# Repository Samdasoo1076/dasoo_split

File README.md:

# choc-split-60 ⌨️

로우스태거(row‑staggered) 배열을 좌우로 나눈 **스플릿 키보드**입니다.
Kailh **Choc v2(CPG1353) 로우프로파일 핫스왑** 스위치 **71개 + 로터리 인코더 1개 = 72키 포지션**
(좌 34 / 우 38), 좌우 각각 **RP2040 Pro Micro**, 안쪽 상단의 **USB-C 링크 포트**로 좌우를 잇고,
`COL2ROW` 매트릭스를 씁니다.
모든 PCB 배선은 자동 라우터 없이 좌표를 계산해 직접 배선했고, `scripts/verify_pcb.py`로 전수 검증합니다.

*(실물 느낌 렌더 — 위 도면 그대로의 배열입니다)*

*(KLE 형식 도면 — 좌우 행 오프셋과 0.25u 매크로 열 간격이 그대로 보입니다)*

*(PCB 미리보기: 빨강 = F.Cu, 파랑 = B.Cu, 흰 점 = 비아, 회색 = F.Silkscreen)*

*(좌 하프 회로도 — 스위치 33 + 다이오드 33, 컨트롤러 U1, USB-C 링크 J1, 리셋, EC11 인코더 RE1과 그 다이오드.
각 칸이 매트릭스의 (행, 열) 자리이고, 넷 이름이 그대로 적혀 있습니다)*

*(우 하프 회로도 — 스위치 38 + 다이오드 38, 컨트롤러·USB-C 링크·리셋. 아래쪽 두 줄의 `← ↓ →` 가 매트릭스
COL6·7·8 에 그대로 놓입니다)*

---

## 1. 보드 사양

| 항목 | 값 |
|---|---|
| 배열 | 65% 로우스태거 + 좌측 매크로 열 + 우측 방향키·Del, 좌우 분리 |
| 키 수 | 좌 33 스위치 + 인코더 1 / 우 38 스위치 = **스위치 71 + 엔코더 1 (72 포지션)** |
| 키 피치 | 19.05 mm (MX 표준 피치, Choc v2 스위치 + MX 호환 키캡) |
| 행 스태거 | 좌 `0 / 0.5u / 0.75u / 1.25u` · 우 `-0.5 / 0 / 0.25 / -0.5u` (Tab 1.5u·Caps 1.75u·LShift 2.25u·`\` 1.5u·RShift **1u**) |
| 분할 위치 | 숫자열 `6`\|`7`, 알파열 `T`\|`Y`, `G`\|`H` — 하단 알파열은 `B` 가 **양쪽 하프에 하나씩** 있습니다(아래 설명) |
| 매크로 열 | 좌측 최외곽 열에서 **0.25u(4.7625 mm)** 띄워 배치, 위→아래 `노브 → Home → End → PgUp → PgDn` |
| 방향키 | `RShift`(1u) 바로 오른쪽 `↑`, 그 아래 `↓`, `↑` 오른쪽에 `Del`, `Del`/`↓` 아래에 `→`, 그 왼쪽 `←`. `RCtrl` 과 `←` 사이는 **0.5u 빈칸**(예전 `RFn` 자리) |
| 스태빌라이저 | **2u 이상 키 5개**에 **Choc v2 PCB 마운트 스태빌**(Salicylic‑acid3 / Keeb‑On! 스크류 타입) — 좌 `LShift`(2.25u)·`Space`(2u) / 우 `BSpc`(2u)·`Enter`(2.25u)·`Space`(2.25u). 키마다 타원 홀 4개(3.2×3.4 / 3.0×4.0 mm, 중심에서 좌우 ±11.9 mm) + 하우징이 지나가는 **Edge.Cuts 컷아웃 2개**(x 8.9~14.9, y ±3.75 mm) = 홀 20 + 컷아웃 10 |
| 스위치 | Kailh Choc v2 (CPG1353), **핫스왑 소켓** (`SW_Hotswap_Kailh_Choc_V2`) — **Choc v1 스위치는 장착 불가**(v1 가이드 페그 홀 제거, v2는 중심 홀 Ø5.0 + 가이드 포스트 1개) |
| 인코더 | Alps EC11 / Bourns PEC11R 호환 5핀 (A·C·B + 푸시 스위치 2핀), 6 mm 축 |
| 다이오드 | 1N4148W SOD-123 × 72 (스위치 71 + 인코더 푸시 1), `COL2ROW` |
| MCU | RP2040 Pro Micro (Elite‑Pi / Pro Micro RP2040 호환, 24핀) × 2 |
| 좌우 연결 | **USB-C 16핀 리셉터클 × 2** (HRO TYPE‑C‑31‑M‑12 규격), 각 하프 **안쪽 상단**에서 케이블이 **위로** 꽂힘. Full‑duplex UART (`VBUS=VCC` / `GND` / `D+=TX` / `D-=RX`, 좌우는 서로 교차) — **링크 전용**, PC에 꽂는 포트 아님 |
| 리셋 | 6×6 택트 스위치 × 2 (RST–GND) |
| PCB | 2층, 1.6 mm, 좌 176×130 mm / 우 181×130 mm, M2 마운팅 홀 각 6개 |
| 펌웨어 | QMK + VIAL (RP2040, `MASTER_LEFT`, `ENCODER_MAP_ENABLE`) |

### 레이아웃

```
       ┌───┐
       │ENC│   ┌───┬───┬───┬───┬───┬───┬───┐
       ├───┤   │Esc│ 1 │ 2 │ 3 │ 4 │ 5 │ 6 │
       │Hom│   ├───┴─┬─┴─┬─┴─┬─┴─┬─┴─┬─┴─┬─┘
       ├───┤   │ Tab │ Q │ W │ E │ R │ T │
       │End│   ├─────┴┬──┴┬──┴┬──┴┬──┴┬──┘
       ├───┤   │ Caps │ A │ S │ D │ F │ G │
       │PgU│   ├──────┴┬──┴┬──┴┬──┴┬──┴┬──┘
       ├───┤   │ LShift│ Z │ X │ C │ V │ B │
       │PgD│   ├───┬───┼───┼──┬┴───┴───┘
       └───┘   │Ctl│Win│Alt│ ␣ Space │      ← 좌측 (34 포지션, Alt 옆 0.5u 빈칸)
               └───┴───┴───┴──┴────────┘
                ↑ 매크로 열과 본열 사이 간격 0.25u
```

우측 하프 (38 포지션). 각 행은 왼쪽 끝이 자기 오프셋에서 시작합니다 — x는 키 단위(u).

| 행 | 시작 x | 키 (왼쪽→오른쪽) | 오른쪽 끝 |
|---|---|---|---|
| Row 0 | **-0.5u** | `7 8 9 0 - =` + `` ` `` + `BSpc` **2.0u** | 8.5u |
| Row 1 | **0.0u** | `Y U I O P [ ]` + `\` 1.5u | 8.5u |
| Row 2 | **0.25u** | `H J K L ; '` + `Enter` 2.25u | 8.5u |
| Row 3 | **-0.5u** | `B` + `N M , . /` + `RShift` 1.0u + `Up` + `Del` | 8.5u |
| Row 4 | **0.25u** | `Space` 2.25u + `RAlt`/`RCtrl` 1.25u×2 + **0.5u 빈칸** + `Left`/`Down`/`Right` | 8.5u |

다섯 행 모두 오른쪽 끝이 **8.5u** 한 줄로 맞습니다 — `BSpc` · `\` · `Enter` · `Del` · `Right` 가 같은 세로선에서 끝납니다.
Row 4 를 0.25u 왼쪽으로 당겨서 맞춘 것이라, `Left`/`Down`/`Right` 는 각각 `RShift`/`Up`/`Del` **바로 아래**에 놓입니다.
`RCtrl`(3.75~5.0u)과 `Left`(5.5u) 사이의 **0.5u 빈칸**은 전에 `RFn` 이 있던 자리입니다.
좌측 하프의 행 오프셋(`0 / 0.5 / 0.75 / 1.25u`)은 ANSI 그대로이고, 우측 하프도 자기 안에서는
ANSI 스태거(`T`|`Y`, `G`|`H`, `B`|`N`)를 그대로 가집니다. 다만 **숫자열은 ANSI보다 1u 왼쪽**에서
시작합니다 — 2u 백스페이스를 지키려고 행을 왼쪽으로 옮겼기 때문입니다. 그래서 두 하프를
숫자열(`6`|`7`)에 맞춰 붙이면 알파열은 1u 벌어지고, 알파열에 맞춰 붙이면 숫자열이 1u 겹칩니다
(서로 다른 두 장이라 겹쳐 놓을 수는 없으니 실제로는 숫자열 기준으로 붙이게 됩니다).

> 하단 알파열은 ANSI 분할선이 `B`|`N` 이라 `B` 가 원래 좌측 하프 끝에 있습니다.
> 이 보드는 **우측 하프 Row 3 왼쪽 끝(x = -0.5u)에도 `B` 를 하나 더** 두었습니다
> (요청에 따라 추가). 그래서 `B` 키는 두 장에 하나씩, 펌웨어에서도 `L35`·`R80` 두 자리가 모두 `KC_B` 입니다.
> 한쪽 `B` 가 필요 없으면 키맵에서 그 자리를 `KC_NO` 로 바꾸면 됩니다.

> 숫자열 `BSpc` 는 **2u 그대로**이고, 그 왼쪽에 **1u `` ` ``** 가 있습니다(요청). 2u 를 지키려고
> 숫자열 전체를 1u 왼쪽으로 옮겼기 때문에 `7` 은 `B` 바로 위, `8` 은 `N` 바로 위에 옵니다.
> 백틱은 우측 하프에만 있고, 좌측 하프의 맨 왼쪽 키는 **`Esc`** 입니다(원래 `` ` `` 자리).

키캡 구성: **1u × 58, 1.25u × 5, 1.5u × 2, 1.75u × 1, 2u × 2, 2.25u × 3** (총 71개) + 노브 1개

---

## 2. 매트릭스와 핀맵

양쪽 PCB 모두 **5행 × 9열** 매트릭스를 쓰고, MCU 핀 배치는 좌우가 완전히 동일합니다.
좌측 매크로 열은 **COL7** 을 쓰고, 인코더 푸시 스위치는 그 열의 Row 0(`L07`)에 들어갑니다.
우측 하프는 `B N M , . / RShift Up Del` 로 9개 키가 필요해 **COL0~COL8** 을 모두 씁니다
(좌측은 COL8이 비어 있습니다).

### MCU 핀 → 네트 (좌/우 동일)

| 핀 | 이름 | 네트 | | 핀 | 이름 | 네트 |
|---|---|---|---|---|---|---|
| 1 | GP0 | `TX` | | 13 | RAW | – (미사용) |
| 2 | GP1 | `RX` | | 14 | GND | `GND` |
| 3 | GND | `GND` | | 15 | RST | `RST` (리셋 스위치) |
| 4 | GND | `GND` | | 16 | VCC | `VCC` (USB-C VBUS) |
| 5 | GP2 | `ROW0` | | 17 | GP29 | `ENC_B` (좌측만) |
| 6 | GP3 | `ROW1` | | 18 | GP28 | `ENC_A` (좌측만) |
| 7 | GP4 | `ROW2` | | 19 | GP27 | `COL8` (우측만) |
| 8 | GP5 | `ROW3` | | 20 | GP26 | `COL7` |
| 9 | GP6 | `ROW4` | | 21 | GP22 | `COL5` |
| 10 | GP7 | `COL0` | | 22 | GP20 | `COL3` |
| 11 | GP8 | `COL1` | | 23 | GP23 | `COL6` |
| 12 | GP9 | `COL2` | | 24 | GP21 | `COL4` |

> 열 순서를 한 줄로 정리하면 `COL0..COL8 = GP7, GP8, GP9, GP20, GP21, GP22, GP23, GP26, GP27` 입니다.
> 우측 PCB는 인코더가 없어서 GP28/GP29가 비어 있고, 그 핀은 풀업 입력으로만 남습니다.
> 좌측 PCB의 `COL8`(GP27)은 키가 없어서 풀업 입력으로만 남습니다.
> 이번 개정에서 예비로 두었던 **GP27을 COL8** 에 배정해 9열을 수용했습니다.

### 키 → (행, 열)

| 행 \ 열 | 0 | 1 | 2 | 3 | 4 | 5 | 6 | 7 | 8 |
|---|---|---|---|---|---|---|---|---|---|
| L0 | 좌 Esc | 1 | 2 | 3 | 4 | 5 | 6 | 좌 ENC | – |
| L1 | 좌 Tab | Q | W | E | R | T | – | 좌 Home | – |
| L2 | 좌 Caps | A | S | D | F | G | – | 좌 End | – |
| L3 | 좌 LShift | Z | X | C | V | B | – | 좌 PgUp | – |
| L4 | 좌 LCtrl | LWin | LAlt | 좌 Space | – | – | – | 좌 PgDn | – |
| R0 | 우 7 | 8 | 9 | 0 | - | = | `` ` `` | BSpc | – |
| R1 | Y | U | I | O | P | [ | ] | \ | – |
| R2 | H | J | K | L | ; | ' | Enter | – | – |
| R3 | 우 B | N | M | , | . | / | RShift | ↑ | Del |
| R4 | 우 Space | RAlt | RCtrl | – | – | – | ← | ↓ | → |

* QMK `MATRIX_ROWS = 10` (좌 0–4 / 우 5–9), `MATRIX_COLS = 9`.
* `R4` 의 3~5열은 비어 있고, `← ↓ →` 는 각각 `RShift`·`↑`·`Del` 과 같은 열(6·7·8)에 들어갑니다.
* 인코더 A/B는 매트릭스가 아니라 **GP28 / GP29** 직결이고, 푸시 스위치만 매트릭스 `L07`에 들어갑니다.

### USB-C 링크 배선 (좌우가 서로 반대)

| USB-C 핀 | 좌측 PCB | 우측 PCB |
|---|---|---|
| VBUS (A4·B4·A9·B9) | `VCC` | `VCC` |
| GND (A1·B1·A12·B12) + 쉴드 4핀 | `GND` | `GND` |
| D+ (A6·B6) | `TX` (GP0) | `RX` (GP1) |
| D- (A7·B7) | `RX` (GP1) | `TX` (GP0) |
| CC1·CC2·SBU1·SBU2 (A5·B5·A8·B8) | – (미연결) | – (미연결) |

> 케이블은 그대로 지나가므로 UART 한 쌍은 **PCB에서 교차**시킵니다. 좌측이 항상 마스터이고
> (`MASTER_LEFT`) USB‑C 케이블은 **좌측**에 꽂습니다.

> **링크 전용(LINK ONLY)**: 이 포트는 좌우를 잇는 5V/GND/D+/D- 전용입니다. 보드 실크에도
> `LINK ONLY` 를 넣었습니다. PC에 꽂으면 5V가 VCC로 역류하고 D+/D-가 PC의 USB 데이터선에 붙습니다.

> **5.1k CC 풀다운은 달지 않았습니다.** ① 이 포트는 장치(PC)와 협상하는 포트가 아니라 두 하프 사이의
> 직결 링크이고, VBUS는 VCC에 그대로 연결돼 있어 C-to-C 케이블로도 5V가 그대로 전달됩니다.
> ② CC를 비워 두면 **C-to-C로 PC에 꽂았을 때 PC가 VBUS를 올려 주지 않으므로**(CC 검출 실패) 역급전이
> 한 겹 막아집니다. ③ 반대로 CC 풀다운을 달면 PC가 이 보드를 장치로 인식해 VBUS를 올리므로 링크
> 포트에 PC를 꽂았을 때 위험해집니다. ④ A-to-C 케이블은 CC와 무관하게 5V가 나오므로 **절대 금지**입니다.
> 나중에 이 포트를 진짜 USB 장치 포트로 쓰려면 CC1·CC2에 5.1k를 GND로 달고 펌웨어를 바꿔야 합니다.

---

## 3. 배선 설계 규칙 (자동 라우터 미사용)

* 행(Row) 버스는 **F.Cu에 가로**로, 열(Col)은 **B.Cu에 세로**로 배선하고, 두 방향이 교차하는 지점은
  비아로 층을 바꿔 같은 층 쇼트를 만들지 않습니다.
* 행 버스는 **키 중심 +10.69 mm에서 한 줄로 곧게** 지나갑니다. 이 높이는 이 행 2u 이상 키의
  앞쪽 타원 홀(아래 끝 `+10.24`)과 바로 아랫줄 2u 이상 키의 뒤쪽 타원 홀(위 끝 `+11.15`) 사이
  0.91 mm 통로의 한가운데라, **홀을 돌아가는 우회 구간이 하나도 없습니다**(양쪽 홀까지 구리 0.325 mm).
* 그 통로는 0.91 mm뿐이라 0.6 mm 비아가 통과할 수 없습니다. 비아 열이 홀 바로 아래에 걸리는 두 곳
  (우측 `]`·`\`)만 비아를 버스 선 위에서 1.87 mm 옆으로 밀고 캐소드가 45도로 한 번 꺾여 들어가며,
  나머지 69개는 캐소드 패드에서 수직으로 바로 내려옵니다.
* 스태빌 타원 홀 20개는 **양면 기판 관통 NPTH**로, 라우터가 트랙·비아를 놓을 때 장애물로 계산합니다
  (스위치 홀·핫스왑 패드·다이오드·마운팅 홀·USB-C/리셋/인코더 패드와 같은 취급).
* 스태빌 **컷아웃 10개(Edge.Cuts 사각 6×7.5 mm)** 는 보드에서 잘려 나가는 영역이라, 라우터가
  트랙·비아를 놓을 때 사각형을 0.70 mm 부풀려 통행 금지 구역으로 잡습니다(실제 구리 이격 0.55 mm 이상 — KiCad 기본 동박-모서리 규칙 0.5 mm도 만족).
* **2u 이상 키의 스위치는 90도 돌려 배치**했습니다. 핫스왑 소켓 패드가 정렬된 채로는 소켓 패드
  2번(x +8.5)이 오른쪽 컷아웃(x 8.9~14.9) 모서리를 파고들고, 소켓 몸체도 스태빌 하우징의 뒤쪽
  돌출부와 부딪힙니다(제작자 Salicylic‑acid3도 "스위치를 옆으로 돌리라"고 안내). 90도 회전 시
  소켓 패드는 x −7.3~+7.3 안에 들어와 컷아웃과 0.2 mm 이상 떨어집니다.
* 다이오드는 스위치 중심에서 **x +6.75 / y +6.5 mm**(일반 키)에 두고, 회전한 2u 키와 인코더는
  **거울 배치(캐소드가 오른쪽)** 로 x **+8.04 / y +5.0 mm** 에 둡니다. 회전 키는 소켓 다리 홀
  (3.05 mm, x +3.81)과 앞쪽 타원 홀(x +10.4) 사이 5.06 mm 틈에 들어가야 해서, 애노드 패드를
  다리 홀에서 0.3 mm, 캐소드 패드를 타원 홀에서 0.31 mm 띄운 자리입니다. 그래서 다이오드와
  **아랫줄 핫스왑 소켓 패드 사이가 2.05 mm → 4.55 mm** 로 벌어졌습니다(SOD-123 몸체와 소켓
  몸체가 조립할 때 서로 부딪히지 않을 여유).
* 다이오드 캐소드의 비아는 **패드 위가 아니라** 패드에서 0.45 mm 아래, 행 버스 선 위에 놓고
  짧은 트랙으로 잇습니다. **패드 위 비아(via-on-pad) 0개** — 비아에서 가장 가까운 패드·홀까지
  0.642 mm 입니다.
* 신호선 **0.25 mm**, 전원(VCC/GND) **0.5 mm**, 비아 **0.6 / 0.3 mm(드릴)**.
* 동일 층 타 네트 교차 0건, 최소 클리어런스 **0.2 mm**, 보드 외곽 이격 **0.3 mm**.
* 모든 트랙은 0/45/90도. 스위치 홀·핫스왑 패드·마운팅 홀·USB-C/리셋/인코더 패드를 장애물로 계산해 회피.
* **USB-C 링크 포트의 0.5 mm 피치 16핀**은 좌표를 직접 계산해 손으로 빼냈습니다. 패드 사이
  (0.5 − 0.3 = 0.2 mm)로는 0.25 mm 트랙도 비아도 지나갈 수 없어, 패드마다 **보드 안쪽으로 직선으로**
  빠져나온 뒤 패드 줄 뒤에서 갈라집니다. D+ (A6/B6)는 A6이 가운데라 이웃 D- 두 줄에 막히므로, B7·A7을 45도로
  바깥으로 벌린 다음 A6 비아를 그 위에 놓고 **B.Cu로 건너가** B6 비아와 잇습니다(0.6 mm 비아가
  0.25 mm 트랙 옆에 서려면 0.625 mm가 필요). VBUS 두 패드는 +3.0 mm에서 F.Cu로 합쳐 비아 하나로
  B.Cu로 내리고, GND는 두 패드와 **쉴드 다리 4개**를 모두 F.Cu로 묶었습니다(쉴드 다리는 패드 줄
  **앞쪽**, 즉 보드 끝 쪽에 있어 좌우 한 줄씩 세로로 이어 GND 패드에 붙였습니다). 나머지 4핀(CC/SBU)은
  미연결입니다.
* 매크로 열 스위치도 나머지 키와 같은 트러스(스위치 → 다이오드 → 비아 → 행 버스)를 그대로 씁니다.
  인코더 푸시 스위치는 `S2 → D_ENC → ROW0` 로 짧게 90도 두 마디로 연결합니다.
* 양면 **GND 존**(F.Cu, B.Cu) + GND는 별도 트랙으로도 전부 연결(존 필 없이도 통전).
* `Edge.Cuts`는 폐곡선(4개 선분)으로 마감, 키·부품과 0.3 mm 이상 이격.

---

## 4. 검증 결과

`scripts/verify_pcb.py`가 생성된 `.kicad_pcb` 파일을 **독립적으로 파싱**해 다음을 전수 검사합니다.

1. 모든 신호 네트 100% 연결(미연결 패드 0건)
2. 동일 층 타 네트 클리어런스 위반 0건 (정확한 폴리곤–세그먼트 거리 계산)
   — **패드에 다른 네트 트랙이 닿는 단락을 따로 보고하는 `check_pad_track()` 포함**
3. 스위치–다이오드 1:1 매칭, 극성(캐소드→행, 애노드→스위치) 일치
4. `Edge.Cuts` 폐곡선 및 외곽 이격
5. 트랙 0/45/90도, 최소 폭, GND 존 존재
6. **2u 이상 스위치마다 Choc v2 스태빌 타원 홀 4개(3.2×3.4 / 3.0×4.0 mm, ±11.9 mm)가
   정확한 위치에 있는지**, v2 가이드 포스트 홀(1.8×2.2 mm 슬롯, 회전 각도 반영)이 있고
   **v1 페그 홀(Ø1.9, ±5.5)이 남아 있지 않은지**, 그리고 그 홀에서 어떤 구리도 0.3 mm 안에
   들어오지 않는지
7. **스태빌 컷아웃 10개가 각각 닫힌 사각 루프이고 보드 안쪽에 있으며, 구리와 0.3 mm 이상
   떨어져 있는지**
8. **패드 위 비아(via-on-pad) 0건**: 모든 비아가 패드 구리·관통 홀 테두리에서 0.30 mm 이상
   떨어져 있는지(같은 네트 패드 포함), 가장 가까운 거리 보고
9. **다이오드가 아랫줄 핫스왑 소켓에서 3 mm 이상** 떨어져 있는지(자기 키 소켓은 제외), 가장
   가까운 거리 보고
10. **USB-C 링크 포트(J1)**: 16핀이 모두 있고 VBUS는 `VCC`, GND 4핀과 **쉴드 다리 4개**는 `GND`,
   D+ (A6/B6)·D- (A7/B7)는 각각 짝이 묶여 서로 다른 UART 넷(`TX`/`RX`)이며 CC/SBU 4핀은 미연결,
   그리고 패드 줄이 보드 **윗변에서 0.3~1.6 mm 안쪽**에 있고 개구부가 −Y(위)를 향하는지

```
$ python3 scripts/verify_pcb.py
======================================================================
checking choc-split-60-left.kicad_pcb
  pads=187 tracks=283 vias=48 nets=55
  stabilizers=2 holes=8 cutouts=4 (nearest copper 1.815 mm)
    SW23  2.25u: 4/4 holes, nearest copper 0.325 mm (3.0 x 4.0 hole at 9.53, 74.91)
    SW33  2.00u: 4/4 holes, nearest copper 0.325 mm (3.0 x 4.0 hole at 88.11, 93.96)
  OK: all checks passed
  via in pad: 48 vias, nearest pad/hole 0.642 mm (via at 62.15, 39.27, hole SW18)
  diode to next row socket: nearest 4.550 mm (D17 to SW24)
  USB-C link USB_C_Receptacle_HRO_TYPE-C-31-M-12: 20 pads centred (143.60, -19.77), pad row 7.23 mm inside the top edge (mouth at the edge), D+ ('TX',) / D- ('RX',)
======================================================================
checking choc-split-60-right.kicad_pcb
  pads=200 tracks=332 vias=62 nets=58
  stabilizers=3 holes=12 cutouts=6 (nearest copper 1.630 mm)
    SW23  2.25u: 4/4 holes, nearest copper 0.325 mm (3.0 x 4.0 hole at 128.59, 55.87)
    SW33  2.25u: 4/4 holes, nearest copper 0.325 mm (3.0 x 4.0 hole at 38.09, 93.96)
    SW8   2.00u: 4/4 holes, nearest copper 0.325 mm (3.0 x 4.0 hole at 130.97, 17.77)
  OK: all checks passed
  via in pad: 62 vias, nearest pad/hole 0.642 mm (via at 52.62, 39.27, hole SW19)
  diode to next row socket: nearest 4.550 mm (D28 to SW35)
  USB-C link USB_C_Receptacle_HRO_TYPE-C-31-M-12: 20 pads centred (-8.90, -19.77), pad row 7.23 mm inside the top edge (mouth at the edge), D+ ('RX',) / D- ('TX',)
```

> 스태빌 타원 홀 20개 중 가장 가까운 구리는 이제 **0.325 mm**(행 버스)로, 바로 옆 통로에 놓인
> 트랙 두 줄과 같은 값입니다. 컷아웃 10개는 가장 가까운 구리에서 **1.815 mm(좌) / 1.630 mm(우)**,
> 비아–패드 최소 **0.642 mm**, 다이오드–아랫줄 소켓 최소 **4.550 mm** — 모두 요구치를 넘고
> 충돌 0건입니다. USB-C 링크 포트는 패드 줄이 윗변에서 **0.5 mm** 안쪽, D+/D-가 각각 `TX`/`RX`
> 한 넷으로 묶여 있고 CC/SBU 4핀은 미연결로 확인됐습니다.

> KiCad DRC가 아니라 자체 기하 검증입니다. 계산 근거는 `scripts/verify_pcb.py`에 그대로 들어 있습니다.
> KiCad 10(웹 ZiroEDA)에서 두 보드 모두 **오류 0 / 미연결 0** 으로 통과했습니다(2026-11-27, 프로젝트 자체 규칙 0.3 mm 기준).
> 같은 보드를 규칙 파일 없이 돌리면 KiCad 기본값(동박-모서리 0.5 mm)이 적용되어 스태빌 컷아웃 주변 구리 몇 곳만
> `copper_edge_clearance`로 남습니다(좌 5 / 우 8) — 모두 스태빌 풋프린트의 컷아웃 주변(부품 자체 치수로 고정된 구간)이라
> 라우팅만으로는 옮길 수 없고,
> 이 보드의 규칙(0.3 mm)과 발주 기준(≥0.3 mm)에는 문제가 없습니다.

---

## 5. BOM

| # | 수량 | 부품 | 비고 |
|---|---|---|---|
| 1 | 2 | RP2040 Pro Micro (Elite‑Pi 등) | 24핀 2.54 mm, **핀 소켓** 사용 권장 |
| 2 | 71 | Kailh Choc **v2 (CPG1353)** 스위치 | 로우프로파일, MX 호환 스템. **Choc v1 스위치는 사용 불가** |
| 3 | 71 | Choc 핫스왑 소켓 (CPG135001S30) | PCB 뒷면, v1/v2 공용 소켓 |
| 4 | 72 | 1N4148W (SOD‑123) | 캐소드(띠) 방향 주의 (D_ENC 포함) |
| 5 | 1 | Alps EC11 / Bourns PEC11R 인코더 (푸시 포함) | 6 mm 축, 너트/와셔 포함품 |
| 6 | 1 | 6 mm D컷 노브 | 인코더 축용 |
| 7 | 2 | USB-C 리셉터클 16핀 (HRO **TYPE‑C‑31‑M‑12**) | 좌우 링크 전용. **플라스틱 로케이팅 포스트 2개는 납땜 전에 밀봉 절단**(이 풋프린트는 그 홀을 뺐습니다 — 아래 설명) |
| 8 | 2 | 6×6×5 mm 택트 스위치 | 리셋 |
| 9 | 12 | M2 나사/너트 | 홀 2.2 mm, 보드당 6개 |
| 10 | 71 | **MX 호환** 로우프로파일 키캡 | 1u 58 / 1.25u 5 / 1.5u 2 / 1.75u 1 / 2u 2 / 2.25u 3 — Choc v1 전용(두 갈래 스템) 키캡은 **장착 불가**, MX 십자 스템용 |
| 11 | 5 | **Choc v2 전용 PCB 마운트 스태빌라이저 2u** (스크류 타입) | 좌 `LShift`·`Space` / 우 `BSpc`·`Enter`·`Space` — Keeb‑On!/Salicylic‑acid3 판매품. **체리 MX 스태빌과 호환 안 됨**, Gateron LP v3에도 사용 가능 |
| 12 | 2 | PCB (2층, 1.6 mm) | 좌 176×130 / 우 181×130 mm |

배선 통계(검증 스크립트 기준)

| | 좌 | 우 |
|---|---|---|
| 트랙 | 283 세그먼트 | 332 세그먼트 |
| 비아 (0.6/0.3 mm) | 48 | 62 |
| 네트 | 55 | 58 |
| 스태빌 타원 홀 | 8 (2키) | 12 (3키) |
| 스태빌 컷아웃 | 4 | 6 |

기계 파일(`BOM.csv`)도 함께 들어 있습니다.

---

## 6. JLCPCB 발주 가이드

1. Gerber: KiCad에서 각 `.kicad_pcb`를 열고 `File → Fabrication Outputs → Gerbers`로 생성
   (2 layer, F.Cu/B.Cu + F.Mask/B.Mask + F.Silkscreen/B.Silkscreen + Edge.Cuts + 드릴 파일).
2. 두 보드는 **서로 다른 PCB**입니다. `choc-split-60-left`, `choc-split-60-right`를 각각 주문하거나,
   같은 주문에 두 파일을 넣을 경우 **패널라이징(별도 PCB로 2종 주문)** 하는 편이 안전합니다.
3. 권장 옵션
   * Layers: 2, Thickness: 1.6 mm, FR‑4
   * Min track/spacing: 0.25 mm / 0.2 mm (본 설계 최소값)
   * Min hole: 0.3 mm (비아 0.3 mm 드릴 사용)
   * Surface finish: HASL (무연)
   * Gold fingers / impedance / castellation: 없음
   * SMT 조립은 하지 않습니다(전 부품 수동 납땜).
4. 주문 전 KiCad 3D 뷰어로 **스위치·MCU·USB-C·인코더 간섭**을 한 번 확인하세요.
   특히 인코더는 보디가 12.4 mm라 1u 자리에 들어가지만, 노브가 키캡보다 높으므로
   케이스 상판을 만들 때 **노브 자리 홀**을 따로 뚫어야 합니다.

---

## 7. 조립

1. **뒷면(B.Cu)** 에 Choc 핫스왑 소켓 71개와 SOD‑123 다이오드 72개를 납땜합니다.
   다이오드의 **캐소드 띠가 비아(행 버스) 쪽**을 향합니다.
2. 앞면에 MCU 핀 소켓(2×12)을 납땜하고 RP2040 Pro Micro를 꽂습니다.
   **USB‑C 커넥터가 보드 바깥쪽 가장자리**를 향하도록 넣으세요(좌: 왼쪽, 우: 오른쪽).
3. **USB-C 링크 리셉터클(J1)** 과 리셋 택트 스위치를 납땜합니다. 커넥터는 보드 **윗변**에
   붙어 있고 개구부가 보드 밖(위)을 향합니다 — 16핀 SMD 패드가 가장자리에서 0.5 mm 안쪽에
   있으니 납땜 후 **돋보기로 브리지(0.5 mm 피치)를 확인**하세요.
   > **중요**: 이 풋프린트는 HRO 도면의 **로케이팅 포스트 홀(Ø0.65, ±2.89 mm)을 뺐습니다**.
   > 그 홀이 VBUS 패드 바로 뒤를 막아 2층 기판에서 VBUS를 빼낼 통로가 없기 때문입니다(VBUS 패드에서
   > 옆 패드까지 0.665 mm). 커넥터 아래면의 **플라스틱 포스트 2개를 니퍼로 PCB 면과 같게 잘라**
   > 평평하게 만든 뒤 올리세요. 쉴드 다리 4개와 SMD 16핀으로 충분히 고정됩니다.
4. **좌측** 매크로 열 맨 위에 EC11 인코더를 꽂아 납땜하고, 너트로 고정한 뒤 노브를 끼웁니다.
   핀 배열은 위에서부터 `A – C – B`(2.5 mm 피치), 반대쪽이 푸시 스위치 `S1 / S2` 입니다.
   > 사용하는 인코더가 PEC11R 계열이 아니면 **핀 피치(2.5 mm)와 마운트 포스트 지름(2.1 mm)** 을
   > 데이터시트로 한 번 확인하세요. 풋프린트는 `libs/choc60.pretty/RotaryEncoder_EC11.kicad_mod`.
5. 스위치를 핫스왑 소켓에 꽂고, 보강판(플레이트)과 케이스를 조립합니다.
   2u/2.25u 키(`LShift`·`Space`·`BSpc`·`Enter`)에는 **Choc v2 전용 PCB 마운트 스태빌라이저**를
   꽂습니다 — 타원 홀 4개 중 4 mm(스크류) 다리는 키 **앞쪽**(사용자 쪽), 3.4 mm(클립) 다리는
   뒤쪽 홀로 들어가고, 하우징은 양옆 **컷아웃**으로 빠집니다. 스태빌 와이어가 키 **앞쪽**에 오도록
   넣으세요. 이 키들의 스위치는 90도 돌아가 있으니(키캡 스템은 십자라 방향 무관) 소켓에 그대로
   꽂으면 됩니다.
   > **주의**: ① 체리 MX용 스태빌은 규격이 달라 **들어가지 않습니다**. ② Choc v1 스위치도
   > **들어가지 않습니다**(중심 홀·가이드 포스트가 다름). ③ 스태빌 하우징이 PCB 아래로 빠지므로
   > **1.6 mm 기판 기준**입니다(1.2 mm는 심 필요).
6. **USB-C 링크 케이블**로 좌우를 연결하고, USB는 **좌측**에 연결합니다. 링크 포트는
   `LINK ONLY` — PC나 충전기에 꽂지 마세요(A-to-C 케이블은 특히 금지).

> **보강판/케이스**: 본 리포에는 케이스·보강판 도면이 없습니다. Choc v2 표준 컷아웃
> (14×14 mm 스위치 홀, 19.05 mm 피치, 1.6 mm 판재)으로 별도 제작하면 됩니다.
> 2u/2.25u 키 자리에는 Choc v2 스태빌용 **플레이트 컷아웃**(20.3×23.8 mm, 양옆 라운드 슬롯)을
> 넣어 주세요 — 같은 저장소의 `Choc_v2_PlateMountStab_2u` 풋프린트를 쓰면 됩니다.
> 스태빌은 하우징이 PCB를 뚫고 내려가므로 **구조상 플레이트리스도 가능**합니다.
> 매크로 열은 본열과 0.25u(4.76 mm) 떨어져 있으니 컷아웃 사이에 4.76 mm 리브가 남습니다.
> 우측 하단 `RCtrl` 과 `←` 사이(0.5u = 9.5 mm), 좌측 하단 `LAlt` 와 `Space` 사이(0.5u)도
> 빈 PCB이니 그 자리는 리브로 남겨 두세요.

> MCU를 납땜으로 PCB에 바로 붙이면 아래쪽 배선과 붙을 수 있습니다. 반드시 **핀 소켓**을 쓰세요.

---

## 8. 펌웨어 (QMK / VIAL)

```
firmware/choc_split_60/
├── choc_split_60.h      # LAYOUT 매크로 (72 포지션) - 스크립트로 생성
├── config.h             # 매트릭스 핀(5x9), COL2ROW, 시리얼, MASTER_LEFT, ENCODERS_PAD
├── info.json            # QMK 메타데이터(핀, 레이아웃, split, encoder) - 스크립트로 생성
├── rules.mk             # SPLIT_KEYBOARD, SERIAL_DRIVER=vendor, ENCODER_ENABLE/ENCODER_MAP_ENABLE
└── keymaps/
    ├── default/keymap.c
    └── vial/{keymap.c, vial.json, config.h}
```

* `info.json`, `vial.json`, `choc_split_60.h`(LAYOUT)는 `scripts/gen_firmware.py`가
  **PCB 레이아웃에서 그대로 생성**합니다.
  배열을 바꾸려면 `scripts/pcbgen/layout.py`만 고치고 스크립트를 다시 돌리면 됩니다.
* **RFn 키가 없으므로 레이어는 스페이스바 홀드**로 들어갑니다.
  * **좌 스페이스 홀드** → `_FN` (F열·숫자열·미디어). 탭하면 그냥 스페이스.
  * **우 스페이스 홀드** → `_NAV` (Y·U·I·O 에 Home/PgDn/PgUp/End). 탭하면 그냥 스페이스.
  * `TAPPING_TERM 180` + `PERMISSIVE_HOLD` 라서 빠르게 탭하면 항상 스페이스가 나갑니다.
    VIAL에서 두 자리를 `KC_SPC` 로 바꿔 일반 스페이스로 쓸 수도 있습니다.
* 인코더는 좌측에만 있고, 푸시 스위치는 매트릭스 `L07`(기본 레이어 `KC_MUTE`)입니다.
* 기본 레이어의 `Esc` 는 좌측 맨 왼쪽, `` ` `` 는 우측 숫자열 `=`·`BSpc` 사이입니다.
  `_FN` 레이어에서는 좌측 그 자리가 `` ` ``, 우측 그 자리는 그대로 `` ` `` 이고
  (`Esc` 는 기본 레이어에 이미 있으므로 `_FN` 에서는 백틱을 준 것), `BSpc` 자리는 `Del` 입니다.
* 엔코더 맵(레이어별 시계/반시계):
  * `_BASE`: 볼륨 다운 / 업
  * `_FN`: Page Down / Page Up
  * `_NAV`: 이전 곡 / 다음 곡

### QMK

```bash
git clone https://github.com/qmk/qmk_firmware
cp -r firmware/choc_split_60 qmk_firmware/keyboards/
cd qmk_firmware
qmk compile -kb choc_split_60 -km default
# 생성된 choc_split_60_default.uf2 를 RPI-RP2 드라이브에 복사
```

### VIAL

```bash
git clone https://github.com/vial-kb/vial-qmk
cp -r firmware/choc_split_60 vial-qmk/keyboards/
cd vial-qmk
make choc_split_60:vial
```

부트로더 진입: 리셋 스위치를 **두 번** 누르거나, 부팅 중 BOOT를 누른 상태로 USB 연결.

---

## 9. 리포지터리 구조

```
pcb/      choc-split-60-{left,right}.kicad_{pro,sch,pcb} + fp-lib-table
libs/     choc60.pretty (Choc v2 핫스왑, SOD-123, Pro Micro RP2040, USB-C 16P, 택트, EC11, M2,
          Stabilizer_Choc_V2_PCBMount_2u)
scripts/  generate_pcb.py (설계·배선 생성), verify_pcb.py (검증), preview.py,
          gen_firmware.py (info.json/vial.json/LAYOUT 헤더 생성), layout_kle.py (KLE 도면),
          export_libs.py
docs/     preview-*.png, detail-*.png (스태빌 확대), layout-kle.png, layout-render.png,
          verification.txt, review/ (동박 면별 PCB 리뷰 이미지, sch-left/right.png 회로도)
firmware/ QMK/VIAL 키보드 정의
BOM.csv, LICENSE
```

### 다시 생성하기

```bash
python3 scripts/generate_pcb.py    # 두 장의 PCB + 회로도 + 프로젝트 파일 재생성
python3 scripts/generate_pcb.py --schematic-only   # 회로도(.kicad_sch)만 다시 그리기
python3 scripts/gen_firmware.py    # info.json / vial.json / choc_split_60.h 재생성
python3 scripts/export_libs.py     # libs/choc60.pretty 갱신
python3 scripts/verify_pcb.py      # 기하 검증(위 4장의 결과가 다시 나옵니다)
python3 scripts/preview.py         # 미리보기 PNG (좌/우)
python3 scripts/layout_kle.py      # KLE 형식 도면 PNG (layout.py 좌표에서 직접)
python3 scripts/sch_images.py      # 회로도 리뷰 PNG (docs/review/sch-left/right.png)
```

`generate_pcb.py`는 KiCad 파일을 직접 쓰고, 배선은 자체 A* 라우터(0.25 mm 그리드, 45도 이동,
비아 0.6/0.3)로 계산합니다. FreeRouting 등 외부 자동 라우터는 사용하지 않습니다.

---

## 10. 변경 이력

**2026-11-25 (9) 좌우 연결 TRRS → USB-C 링크 포트 (상단 안쪽)**
* 좌우 연결 커넥터를 **TRRS PJ‑320A(3.5 mm 4극)** 에서 **USB-C 16핀 리셉터클**(HRO `TYPE-C-31-M-12`
  규격, KiCad `Connector_USB` 풋프린트)로 바꿨습니다. 부품은 `libs/choc60.pretty/` 에
  `USB_C_Receptacle_HRO_TYPE-C-31-M-12.kicad_mod` 로 들어 있습니다.
* 위치를 각 하프의 **안쪽 상단 가장자리**로 옮겼습니다 — 좌 보드는 오른쪽 위(`x 143.6`), 우 보드는
  왼쪽 위(`x -8.9`). HRO `TYPE-C-31-M-12` 는 **개구부가 +Y, 16핀 패드가 뒤쪽(-Y)** 이라 **180도 돌려**
  배치했고(`y -23.81`), 개구부가 보드 **윗변**을 향해 케이블이 **위에서** 꽂힙니다. 권장 레이아웃대로
  보드 끝을 로케이팅 홀 선에서 5.79 mm 앞에 두어 **몸체가 윗변 밖으로 0.46 mm** 살짝 나오고,
  16핀 패드 줄은 윗변에서 **7.23 mm** 안쪽입니다.
* 신호는 `VBUS`(A4·B4·A9·B9) = `VCC`, `GND`(A1·B1·A12·B12) + **쉴드 다리 4개** = `GND`,
  `D+`(A6·B6) / `D-`(A7·B7) = UART `TX`/`RX`(좌우는 서로 교차). `CC1·CC2·SBU1·SBU2` 는 **미연결**
  — 5.1k CC 풀다운은 달지 않았습니다(이유는 2절 “USB-C 링크 배선”).
* 실크에 **`LINK ONLY`** 를 커넥터 옆(보드 안쪽을 향한 쪽)에 세로로 넣어 이 포트가 PC용이 아님을
  표시했습니다.
* 0.5 mm 피치 16핀은 패드 사이(0.2 mm)로 트랙도 비아도 못 지나가므로, `build_usbc_fanout()` 에
  **손 팬아웃**을 넣었습니다: D- 두 줄(B7·A7)을 45도로 벌려 A6 비아 자리를 만들고, A6/B6는
  **B.Cu 한 줄**로 묶고, VBUS 두 패드는 보드 안쪽 7.05 mm에서 합쳐 비아 하나로 B.Cu로 내리며, GND는
  쉴드 4다리까지 F.Cu로 묶었습니다.
* **로케이팅 포스트 홀(Ø0.65, ±2.89 mm)은 뺐습니다.** VBUS 패드 바로 뒤를 막고 있어 2층 기판에서
  VBUS가 나갈 통로가 없습니다(VBUS 패드 옆 간격 0.665 mm < 필요한 0.75 mm). 커넥터 아래면의
  **플라스틱 포스트 2개를 니퍼로 잘라** 평평하게 만든 뒤 납땜하세요.
* 커넥터가 들어간 자리 때문에 상단 마운팅 홀을 옮겼습니다 — 좌 `x 146 → 130`, 우 `x -6 → 6`
  (같은 윗변 띠, 커넥터·팬아웃과 7 mm 이상).
* 검증기에 **항목 10(USB-C 핀·넷·방향·윗변 위치)** 을 추가했습니다. 결과: 좌 pads 187 · tracks 283 ·
  vias 48 / 우 pads 200 · tracks 332 · vias 62, **미연결 0 · 클리어런스 위반 0 · via-on-pad 0**.
* 라우터도 한 군데 손봤습니다. **네트가 없는 패드**(미사용 CC/SBU)를 장애물 지도에 하드 블록으로
  넣었습니다. 0.5 mm 피치에서는 이웃 패드의 부풀린 금지 구역이 겹치는데, 장애물 지도가 셀마다
  네트를 하나만 기억해서 **다른 네트 패드의 구역이 같은 네트 패드 구역에 덮여** 지워지면 그 틈으로
  트랙이 지나갈 수 있었습니다(우측 하프에서 실제로 발생 → 검증기가 잡음).
* 회로도 J1도 16핀 + 쉴드 심볼로 바꾸고 CC/SBU 4핀에 no-connect를 표시했습니다.

**2026-11-25 (8) 회로도 리뷰 이미지**
* `docs/review/sch-left.png` · `sch-right.png` — A3 회로도 한 장을 **4621 × 3268 px(11 px/mm)** 로
  렌더한 리뷰용 이미지. 심볼 외곽선·핀 번호·핀 이름·레퍼런스·값, 모든 와이어와 넷 라벨
  (ROW0‑4 / COL0‑8 / K1‑33 / UART TX·RX / VCC / GND / ENC_A·B / K_ENC / RST)이 겹침 없이 읽힙니다.
* `kicad-cli` 없이 `.kicad_sch` 를 직접 읽어 그리는 `scripts/sch_images.py` 를 추가했습니다.
  문자열마다 잃크 박스를 기록해 **텍스트 겹침 0건 · 시트 밖 문자열 0건**을 스스로 검사하고,
  겹치면 0이 아닌 종료 코드로 끝납니다(`--check` 는 이미지 없이 검사만).
* 회로도 배치를 다시 잡았습니다. 각 키를 **자기 매트릭스 (행, 열) 자리**에 놓아 한 줄이 한 행이 되고,
  값·레퍼런스를 심볼 위/아래로 분리해 겹침을 없앴습니다(기존에는 스위치 값과 다이오드 레퍼런스가
  0.84 mm 간격으로 포개졌습니다). 왼쪽 넷 라벨은 심볼 바깥쪽으로 정렬을 뒤집었습니다.
* `\` 키의 값이 S‑expression 에서 백슬래시 하나로 나가 KiCad 가 문자열을 잘못 읽던 문제를 고쳐
  `\\ (1.50u)` 로 이스케이프했습니다.
* 회로도만 다시 쓰는 `python3 scripts/generate_pcb.py --schematic-only` 를 추가했습니다(라우팅된
  PCB 는 건드리지 않고 시트 uuid 도 유지).

**2026-11-25 (7) 패드 위 비아 제거 · 다이오드 이격 · 행 버스 정리** (r/ErgoMechKeyboards 피드백 반영)
* **패드 위 비아(via-on-pad)를 전부 없앴습니다.** 다이오드 72개의 캐소드 비아가 1.3×1.5 mm 캐소드
  패드 한가운데에 박혀 있었습니다. 이제 비아는 패드에서 0.45 mm 아래, 행 버스 선 위에 있고
  짧은 캐소드 트랙으로 이어집니다. 비아 100개 전수 검사에서 가장 가까운 패드·홀까지 **0.642 mm**,
  패드와 겹치는 비아 0건입니다(검증기에 항목 8 추가).
* **다이오드를 스위치 쪽으로 올려 아랫줄 핫스왑 소켓과의 거리를 2.05 → 4.55 mm로** 벌렸습니다
  (일반 키 y +9.0 → +6.5, 회전 키·인코더는 거울 배치로 y +5.0 / x +8.04). SOD-123 몸체와
  소켓 몸체가 조립 중에 서로 간섭할 여지가 없어졌습니다(검증기에 항목 9 추가).
* **행 버스의 스태빌 홀 우회를 없앴습니다.** 버스를 키 중심 **+10.69 mm** 한 줄로 내려, 앞쪽
  타원 홀(+10.24)과 아랫줄 뒤쪽 타원 홀(+11.15) 사이 0.91 mm 통로 한가운데로 곧게 지나가게
  했습니다. 5개 행 모두 사선 한 번 없이 곧은 직선이고, 45도 지그재그·사각 우회 0건입니다.
  통로가 0.6 mm 비아보다 좁아 비아가 홀 아래에 걸리는 두 열은 비아만 1.87 mm 옆으로 밀었습니다.
* 비아–홀 최소 0.325 mm(트랙 0.25 mm 기준), 컷아웃 최소 **1.630 mm(우)** 로 이전(2.151 mm)보다
  가까워졌지만 요구치 0.30 mm 는 그대로 넘습니다.
* 검증 결과: 미연결 0, 동일 층 클리어런스 위반 0, via-on-pad 0, 다이오드–소켓 최소 4.55 mm.

**2026-11-25 (6) Choc v2 전환 · Choc v2 PCB 마운트 스태빌**
* 스위치를 **Kailh Choc v2 (CPG1353)** 로 전환했습니다. 핀·소켓 좌표는 v1과 같아서(Kailh
  `CPG135301D01`) 소켓 패드·관통 홀은 그대로이고, **중심 홀 Ø5.05**, **v2 가이드 포스트 홀
  1.8×2.2 mm 슬롯 1개**(-5, +5.15)만 남기고 **v1 가이드 페그 홀(Ø1.9, ±5.5)을 제거**했습니다.
  → **Choc v1 스위치는 이 기판에 장착할 수 없습니다.**
* 키캡은 Choc v1 전용(두 갈래)이 아니라 **MX 호환 십자 스템**용이어야 합니다.
* 스태빌라이저를 **체리 MX PCB 마운트 → Choc v2 전용 PCB 마운트 2u**(Salicylic‑acid3 /
  Keeb‑On! 스크류 타입)로 교체했습니다. 키마다 **타원 홀 4개**(3.2×3.4 / 3.0×4.0 mm, ±11.9 mm)와
  하우징이 지나가는 **Edge.Cuts 컷아웃 2개**(6×7.5 mm, x 8.9~14.9 / y ±3.75)를 넣어
  좌 4 + 우 6 = **홀 20 + 컷아웃 10**입니다.
* **2u 이상 키 5개의 스위치를 90도 회전**했습니다. 정렬 배치에서는 핫스왑 소켓 패드 2번이 컷아웃
  모서리와 겹치고(0.9×1.2 mm), 소켓 몸체가 스태빌 하우징 뒤쪽 돌출부와 간섭합니다. 회전하면
  소켓 패드가 안쪽으로 들어와 컷아웃과 0.2 mm 이상, 홀과 0.32 mm 이상 떨어집니다.
* 회전 키의 다이오드를 x 6.75 → **7.68 mm** 로 밀고, 스위치→다이오드 스텁을 캐소드 **아래로
  우회**시켜 애노드에 붙였습니다(캐소드·비아 관통 회피, 클리어런스 0.2 mm 이상).
* 행 버스는 새 타원 홀(3.0×4.0)에서 45도로 우회하고, 컷아웃 주변은 라우터가 0.5 mm 부풀린
  금지 구역으로 처리합니다. 자체 검증: 미연결 0, 클리어런스 위반 0, 홀 최소 0.320 mm,
  컷아웃 최소 1.815 mm(좌)/2.151 mm(우).

**2026-11-24 (5) 2u 백스페이스 복귀 · 0.5u 간격 · 스태빌 홀**
* `BSpc` 를 **2u 로 되돌렸습니다**. 대신 우측 **숫자열 전체를 1u 왼쪽으로**(시작 `-0.5u`) 옮겨서
  `7 8 9 0 - =` + 1u `` ` `` + **2u `BSpc`** 가 되고 오른쪽 끝은 8.5u 그대로입니다.
  그래서 `7` 은 `B` 바로 위, `8` 은 `N` 바로 위에 옵니다.
* 우측 **Row 4 시작을 `0.5u` → `0.25u`** 로 0.25u 더 당겨 `RCtrl` 이 5.0u 에서 끝나고,
  `RCtrl`(3.75~5.0u) 과 `Left`(5.5u) 사이가 정확히 **0.5u** 가 됩니다.
* 좌측 **`Space` 를 0.5u 오른쪽으로**(3.75~5.75u → **4.25~6.25u**) 옮겨 `LAlt` 와의 간격도 **0.5u**.
* **2u 이상 키 5개에 체리 MX PCB 마운트 스태빌 홀**을 넣었습니다(좌 `LShift`·`Space`,
  우 `BSpc`·`Enter`·`Space` = 20 홀). 규격은 `Stabilizer_Cherry_MX_2.00u` 그대로 —
  중심에서 좌우 **±11.938 mm**, 뒤쪽 **3.048 mm** 위치결정 홀(`cy - 6.985`),
  앞쪽 **3.9878 mm** 마운트 홀(`cy + 8.225`)입니다. 풋프린트는
  `libs/choc60.pretty/Stabilizer_Cherry_MX_2.00u.kicad_mod`.
* 행 버스가 2u 이상 키의 마운트 홀을 만나면 **45도로 위로 비켜 갑니다**(홀 테두리에서 0.5 mm).
  라우터도 이 홀 20개를 양면 관통 장애물로 계산하고, 검증기는 홀 위치와 구리 이격을 따로
  확인합니다 — 가장 가까운 구리 **0.350 mm**, 충돌 **0건**.
* 키캡 **1u 59 → 58**, **2u 1 → 2**, 스태빌 **플레이트 마운트 4 → 체리 MX PCB 마운트 5**.
  매트릭스(5×9), 스위치 71 · 다이오드 72 · 인코더 1 은 그대로입니다.
* 펌웨어 JSON 도면은 두 하프를 숫자열 기준으로 붙인 위치(`RIGHT_OFFSET 6.5 → 7.5`)로 그립니다.

**2026-11-24 (4) Esc · 백틱 · 우측 끝 8.5u 칼정렬**
* 좌측 하프 맨 왼쪽 키를 `` ` `` → **`Esc`** 로 바꿨습니다(라벨·펌웨어·도면만, PCB 좌표는 그대로).
* 우측 하프 숫자열 `=` 오른쪽에 **1u `` ` ``** 를 넣고 `BSpc` 를 **2u → 1u** 로 줄였습니다.
  Row 0 은 `7 8 9 0 - =` + `` ` `` + `BSpc` 8 키가 되고 오른쪽 끝은 8.5u 그대로입니다.
* 우측 Row 3 시작을 `-0.25u` → **`-0.5u`**, Row 4 시작을 `0.75u` → **`0.5u`** 로 0.25u씩 왼쪽으로 당겼습니다.
  그래서 `Del` · `Right` 도 **8.5u** 에서 끝나 **다섯 행의 오른쪽 끝이 한 세로선**으로 맞고,
  `Left`/`Down`/`Right` 는 각각 `RShift`/`Up`/`Del` 바로 아래에 놓입니다.
* 우측 보드 외곽선을 새 키 범위(`-0.5u ~ 8.5u`)에 맞춰 4.76 mm 왼쪽으로 옮겼습니다(폭은 181 mm 그대로).
  오른쪽이 0.25u 좁아져 가장자리 마운팅 홀 하나를 하단 띠(`x = 160 mm`)로 옮겼습니다.
* 스위치 **70 → 71**, 다이오드·핫스왑 소켓 **71 → 72**, 키캡 **1u 57 → 59**, **2u 2 → 1**,
  스태빌라이저 **5 → 4**. 매트릭스는 5행×9열 그대로입니다.
* 펌웨어: 좌 `L00` = `KC_ESC`, 우 `R56` = `` ` ``(`KC_GRV`), `R57` = `KC_BSPC`.

**2026-11-24 (3) 우측 B · Del · 1u RShift · 0.25u 간격**
* `RShift` 를 **1.75u → 1.0u** 로 줄이고 바로 오른쪽에 `↑` 를 붙였습니다.
* 우측 하프 Row 3 왼쪽 끝(**x = -0.25u**)에 **`B`** 를 추가했습니다(`N` 바로 왼쪽, `Y` 보다 0.25u 왼쪽).
  그래서 이 행은 `B N M , . / RShift ↑ Del` 9키가 되고, `↑` 오른쪽 빈자리에 요청대로
  **1u `Del`** 을 넣었습니다.
* **`RFn` 키를 제거**했습니다. 하단 열은 `Space 2.25u + RAlt/RCtrl 1.25u×2`(끝 5.5u)
  → **0.25u 빈칸** → `← ↓ →` 로 바뀌었고, `← ↓ →` 는 각각 `RShift`·`↑`·`Del` 바로 아래에 놓입니다.
* 레이어 접근은 스페이스 홀드로 옮겼습니다(좌 `_FN`, 우 `_NAV`). 자세한 내용은 8절.
* 매트릭스를 **5행×8열 → 5행×9열**(좌우 합 10×9)로 늘리고, 예비였던 **GP27 을 `COL8`** 에 배정했습니다.
* 우측 하프 폭을 **195 → 181 mm** 로 다시 줄였습니다(`B` 가 왼쪽으로, `Right` 가 8.75u 로 들어와서).
  마운팅 홀도 새 키 위치에 맞춰 재배치했습니다.
* `choc_split_60.h`(LAYOUT)도 이제 `scripts/gen_firmware.py`가 생성합니다.

**2026-11-24 (2) 우측 행 스태거 수정**
* 우측 PCB의 다섯 행이 전부 `x = 0`에서 시작해 **일직선(오쏘리니어처럼)** 보이던 문제를 고쳐
  표준 ANSI **로우스태거**를 넣었습니다. 오프셋은 `0.5 / 0 / 0.25 / 0.75u`,
  분할선은 숫자열 `6`|`7`, `T`|`Y`, `G`|`H`, `B`|`N`입니다.
* Row 0~3의 오른쪽 끝을 전부 **8.5u**로 맞췄습니다. 그래서 `\` 는 1u → **1.5u**
  (좌측 Tab과 같은 규격)로 넓혔습니다.
* 하단 열은 `Space 2.25u + RAlt/RFn/RCtrl 1.25u×3` 으로 정확히 **6.5u**에서 끝나고,
  그 뒤로 `← 6.5 / ↓ 7.5 / → 8.5~9.5u` 가 붙습니다. `↓`는 `↑`(7.5~8.5u) 바로 아래입니다.
* 보드 폭을 **182 → 195 mm** 로 늘려 `→` 키가 외곽선 밖으로 나가지 않게 했고, 마운팅 홀도 다시 배치했습니다.
* `docs/layout-kle.png`(KLE 도면)와 `docs/layout-render.png`(실물 렌더)를 새로 넣고 README에 올렸습니다.

**2026-11-24 (1)**
* 스페이스바 아래에 돌출돼 있던 **Th1/Th2 썸키 4개를 제거**하고, 보드를 그만큼 줄였습니다
  (좌 160×143 → 176×130 mm, 우 175×143 → 182×130 mm).
* 좌측 최외곽 열에서 **0.25u 왼쪽**에 1u 폭 세로 열을 새로 만들고 위에서부터
  **로터리 인코더 · Home · End · Page Up · Page Down** 을 넣었습니다.
* 우측 하단에 **방향키 `← ↓ →` + 그 위의 `↑`** 를 넣었습니다(RShift는 1.75u 유지).
* 매트릭스를 **6행×8열 → 5행×8열**(좌우 합 10×8)로 정리하고, 열을 하나 늘리지 않기 위해
  매크로 열은 비어 있던 좌측 `COL7`에 배정했습니다.
* 여유 GPIO가 정확히 2개 남아 **GP28/GP29를 인코더 A/B**에 배정했습니다(더미 핀 없음).

**2026-11-23** 65키 로우스태거 스플릿 초판.

---

## 11. 크레딧

* Choc v1/v2 공용 핫스왑 소켓 풋프린트 형상: [keyswitch-kicad-library](https://github.com/perigoso/keyswitch-kicad-library) (CC‑BY‑SA‑4.0)
* Choc v2 스위치 홀 규격: Kailh `CPG135301D01` 도면 (중심 Ø5.00, 핀 2개 동일, 가이드 포스트 Ø1.60 1개)
* Choc v2 PCB 마운트 스태빌 풋프린트: [Salicylic-acid3/KiCAD_FootPrint](https://github.com/Salicylic-acid3/KiCAD_FootPrint) `kbd_Stabilizer.pretty/Choc_v2_PCBMountStab_2u.kicad_mod` (사용 안내: https://salicylic-acid3.hatenablog.com/entry/chocv2-stab-guide)
* USB-C 리셉터클 풋프린트: [KiCad Connector_USB](https://github.com/KiCad/kicad-footprints) `USB_C_Receptacle_HRO_TYPE-C-31-M-12` (HRO `TYPE-C-31-M-12` 도면, 로케이팅 포스트 홀 2개만 생략)
* EC11 인코더 패드 좌표: Bourns PEC11R 데이터시트 (A–C–B 2.5 mm 피치, 마운트 2.1 mm)
* QMK / VIAL 펌웨어

라이선스: **CC BY‑SA 4.0** (`LICENSE` 참고)

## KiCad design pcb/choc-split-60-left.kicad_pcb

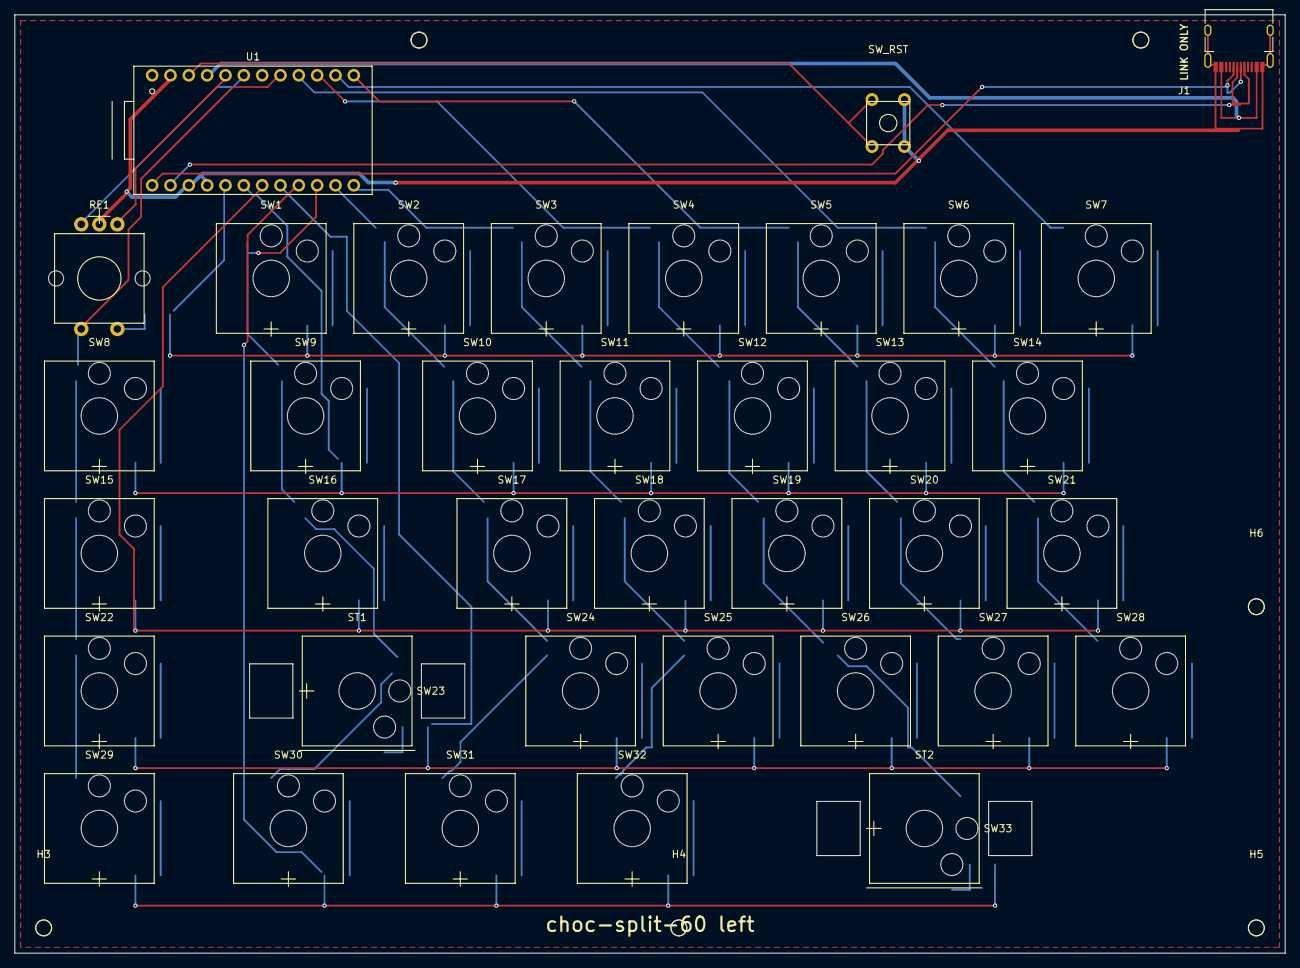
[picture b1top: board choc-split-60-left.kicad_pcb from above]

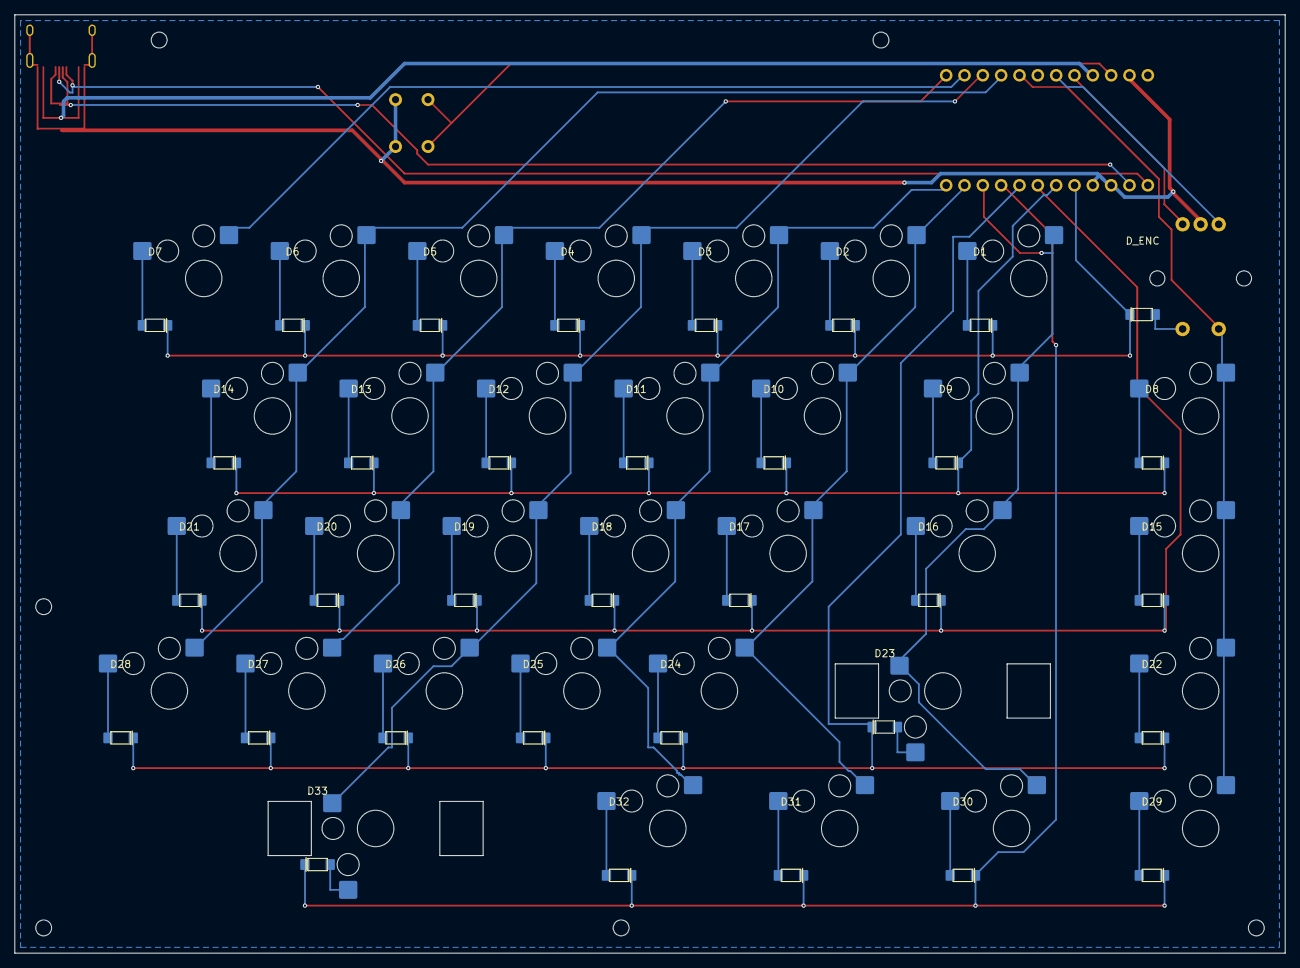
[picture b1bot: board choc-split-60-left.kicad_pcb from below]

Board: 2 copper layers, 176.0 x 130.0 mm, 79 parts (34 on the bottom side), 54 nets.

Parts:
D1, D2, D3, D4, D5, D6, D7, D8, D9, D10, D11, D12, D13, D14, D15, D16, D17, D18, D19, D20, D21, D22, D23, D24, D25, D26, D27, D28, D29, D30, D31, D32, D33: 1N4148W; D_SOD-123
D_ENC: 1N4148W; D_SOD-123
H1, H2, H3, H4, H5, H6: M2; MountingHole_M2
J1: USB-C 16P link; USB_C_Receptacle_HRO_TYPE-C-31-M-12
RE1: EC11 rotary encoder; RotaryEncoder_EC11
ST1, ST2: Choc v2 stab 2u; Stabilizer_Choc_V2_PCBMount_2u
SW1, SW2, SW3, SW4, SW5, SW6, SW7, SW8, SW10, SW11, SW12, SW13, SW14, SW15, SW17, SW18, SW19, SW20, SW21, SW22, SW24, SW25, SW26, SW27, SW28, SW29: ChocV2 1.00u; SW_Hotswap_Kailh_Choc_V2_1.00u
SW9: ChocV2 1.50u; SW_Hotswap_Kailh_Choc_V2_1.50u
SW16: ChocV2 1.75u; SW_Hotswap_Kailh_Choc_V2_1.75u
SW23: ChocV2 2.25u; SW_Hotswap_Kailh_Choc_V2_2.25u
SW30, SW31, SW32: ChocV2 1.25u; SW_Hotswap_Kailh_Choc_V2_1.25u
SW33: ChocV2 2.00u; SW_Hotswap_Kailh_Choc_V2_2.00u
SW_RST: Reset; SW_Reset_6mm
U1: RP2040 Pro Micro; ProMicro_RP2040

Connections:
COL0: SW1.1, SW9.1, SW16.1, SW23.1, SW30.1, U1.10 (GP7)
COL1: SW2.1, SW10.1, SW17.1, SW24.1, SW31.1, U1.11 (GP8)
COL2: SW3.1, SW11.1, SW18.1, SW25.1, SW32.1, U1.12 (GP9)
COL3: SW4.1, SW12.1, SW19.1, SW26.1, SW33.1, U1.22 (GP20)
COL4: SW5.1, SW13.1, SW20.1, SW27.1, U1.24 (GP21)
COL5: SW6.1, SW14.1, SW21.1, SW28.1, U1.21 (GP22)
COL6: SW7.1, U1.23 (GP23)
COL7: RE1.S1, SW8.1, SW15.1, SW22.1, SW29.1, U1.20 (GP26)
ENC_A: RE1.A, U1.18 (GP28)
ENC_B: RE1.B, U1.17 (GP29)
GND: J1.A1, J1.A12, J1.B1, J1.B12, J1.S1 (SHIELD), RE1.C, SW_RST.2, SW_RST.4, U1.3 (GND), U1.4 (GND), U1.14 (GND)
K1: D1.2 (A), SW1.2
K2: D2.2 (A), SW2.2
K3: D3.2 (A), SW3.2
K4: D4.2 (A), SW4.2
K5: D5.2 (A), SW5.2
K6: D6.2 (A), SW6.2
K7: D7.2 (A), SW7.2
K8: D8.2 (A), SW8.2
K9: D9.2 (A), SW9.2
K10: D10.2 (A), SW10.2
K11: D11.2 (A), SW11.2
K12: D12.2 (A), SW12.2
K13: D13.2 (A), SW13.2
K14: D14.2 (A), SW14.2
K15: D15.2 (A), SW15.2
K16: D16.2 (A), SW16.2
K17: D17.2 (A), SW17.2
K18: D18.2 (A), SW18.2
K19: D19.2 (A), SW19.2
K20: D20.2 (A), SW20.2
K21: D21.2 (A), SW21.2
K22: D22.2 (A), SW22.2
K23: D23.2 (A), SW23.2
K24: D24.2 (A), SW24.2
K25: D25.2 (A), SW25.2
K26: D26.2 (A), SW26.2
K27: D27.2 (A), SW27.2
K28: D28.2 (A), SW28.2
K29: D29.2 (A), SW29.2
K30: D30.2 (A), SW30.2
K31: D31.2 (A), SW31.2
K32: D32.2 (A), SW32.2
K33: D33.2 (A), SW33.2
K_ENC: D_ENC.2 (A), RE1.S2
ROW0: D1.1 (K), D2.1 (K), D3.1 (K), D4.1 (K), D5.1 (K), D6.1 (K), D7.1 (K), D_ENC.1 (K), U1.5 (GP2)
ROW1: D8.1 (K), D9.1 (K), D10.1 (K), D11.1 (K), D12.1 (K), D13.1 (K), D14.1 (K), U1.6 (GP3)
ROW2: D15.1 (K), D16.1 (K), D17.1 (K), D18.1 (K), D19.1 (K), D20.1 (K), D21.1 (K), U1.7 (GP4)
ROW3: D22.1 (K), D23.1 (K), D24.1 (K), D25.1 (K), D26.1 (K), D27.1 (K), D28.1 (K), U1.8 (GP5)
ROW4: D29.1 (K), D30.1 (K), D31.1 (K), D32.1 (K), D33.1 (K), U1.9 (GP6)
RST: SW_RST.1, SW_RST.3, U1.15 (RST)
RX: J1.A7, J1.B7, U1.2 (GP1)
TX: J1.A6, J1.B6, U1.1 (GP0)
VCC: J1.A4, J1.A9, J1.B4, J1.B9, U1.16 (VCC)
